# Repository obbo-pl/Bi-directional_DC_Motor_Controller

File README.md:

# Bi-directional_DC_Motor_Controller
RC Bi-directional DC Motor Speed Controller

##### Main features:

- supply voltage: 7.0 - 20.0V,
- average current: 10A, maximum instantaneous current: 140A,
- BEC 5V 1,2A,
- protection against reverse battery polarity,
- on/off switch controlled by logic level,
- calibration of the adjustment range with automatic saving of settings,
- protection against engine starting when starting the system,
- Cut-off, engine shutdown or speed reduction,
- choice of: linear and nonlinear RPM control characteristics,
- speed regulation smoothing filter,
- Fail-safe, engine shutdown in the event of signal loss,
- 3 quick configuration jumpers,
- brake,
- parameter configuration via serial port (9600bps).

### Hardware & Firmware.

These sections provide information on building a hardware, including schematics, PCBs, and firmware.

For more information: [www.obbo.pl](http://obbo.pl/dc-controller)

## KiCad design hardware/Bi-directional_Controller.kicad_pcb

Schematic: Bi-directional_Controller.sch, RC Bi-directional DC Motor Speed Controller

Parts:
B1: bead; L_0805K
C1, C9: 100n; C_0805_2012Metric
C4, C5, C8, C10: 100n; C_Disc_D5.0mm_W2.5mm_P5.00mm_PAD
C6, C7: 15p; C_0805_2012Metric
C11: 100u/35V; CP_Elec_6.3x5.9
C12: 1000u/10V; CP_Elec_10x10
D1: B340; D_SMB
D2: LED; LED_0805_2012Metric_Pad1.15x1.40mm_HandSolder
D3: 4V7; D_MiniMELF
D4: 8v2; D_MiniMELF
J1: ON/OFF; PinHeader_1x02_P2.54mm_Vertical_PAD
J2: Conn_01x06; PinHeader_1x06_P2.54mm_Vertical_PAD
J3: Conn_02x03_Odd_Even; PinHeader_2x03_P2.54mm_Vertical_SMD
J7: BAT 12V; TerminalBlock_Degson_DG128-5.0-02P
J8: CH1; PinHeader_1x03_P2.54mm_Vertical_PAD
J13: MOTOR; TerminalBlock_Degson_DG128-5.0-02P
J14: Serial; PinHeader_1x03_P2.54mm_Vertical_PAD
L1: 100uH; L_SMD_Ferrite_X13mm_Y10mm_H5mm_HandSoldering
Q1, Q2: BSS138; SOT-23
Q3, Q4, Q5, Q6: AOD403; TO-252-2-DPAK
Q7, Q8, Q9, Q10: AOD240; TO-252-2-DPAK
Q12: AO6401A; TSOP-6_1.65x3.05mm_P0.95mm
R1, R18: 330; R_0805_2012Metric
R2, R3, R11, R15: 10k; R_0805_2012Metric
R10: 22k*; R_0805_2012Metric
R12, R26: 4k7; R_0805_2012Metric
R13, R14, R24, R25: 22k; R_0805_2012Metric
R16: 11k*; R_0805_2012Metric
R17, R20: 220; R_0805_2012Metric
R19, R21: 22k; R_Axial_DIN0207_L6.3mm_D2.5mm_P10.16mm_Horizontal_PAD
R22, R23: 220; R_Axial_DIN0207_L6.3mm_D2.5mm_P10.16mm_Horizontal_PAD
SW1: RESET; SW_SPST_PTS645
U1: LM2576HVS-5; TO-263-5_TabPin6
U2: ATmega8-16AU; TQFP-32_7x7mm_P0.8mm
Y1: 16MHz; Crystal_SMD_HC49-SD_HandSoldering

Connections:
+5V: B1.1, C5.1, C12.1, J2.4, J8.2, L1.2, R11.1, R15.2, U2.4 (VCC), U2.6 (VCC)
+12V: C10.1, C11.1, D4.1 (K), Q12.4, R2.2, R10.1, U1.1 (VIN)
CH1: R1.1, U2.9 (PD5)
DIR_L: R20.2, U2.13 (PB1)
DIR_R: R17.2, U2.14 (PB2)
GND: C1.2, C4.2, C5.2, C6.2, C7.2, C8.2, C9.2, C10.2, C11.2, C12.2, D1.2 (A), D2.1 (K), D3.2 (A), J1.1, J2.5, J3.2, J3.4, J3.6, J7.2, J8.1, J14.3, Q1.2 (S), Q2.2 (S), Q7.3, Q8.3, Q9.3, Q10.3, R3.1, R12.2, R16.2, R19.1, R21.2, R24.1, R25.1, R26.1, SW1.1, U1.3 (GND), U2.3 (GND), U2.5 (GND), U2.21 (AGND)
unnamed: B1.2, C8.1, U2.18 (AVCC)
unnamed: C4.1, J2.6, R11.2, SW1.2, U2.29 (PC6/~RESET)
unnamed: C6.1, U2.7 (PB6/XTAL1), Y1.1
unnamed: C7.1, U2.8 (PB7/XTAL2), Y1.2
unnamed: C9.1, U2.20 (AREF)
unnamed: D1.1 (K), L1.1, U1.2 (OUT)
unnamed: D2.2 (A), R18.2
unnamed: D4.2 (A), Q12.3, R3.2
unnamed: J1.2, R2.1, U1.5 (~ON~/OFF)
unnamed: J2.1, U2.15 (PB3)
unnamed: J2.2, U2.16 (PB4)
unnamed: J2.3, U2.17 (PB5)
unnamed: J3.1, U2.12 (PB0)
unnamed: J3.3, U2.11 (PD7)
unnamed: J3.5, U2.10 (PD6)
unnamed: J8.3, R1.2
unnamed: J13.1, Q3.2, Q4.2, Q7.2, Q8.2
unnamed: J13.2, Q5.2, Q6.2, Q9.2, Q10.2
unnamed: J14.1, U2.30 (PD0)
unnamed: J14.2, U2.31 (PD1)
unnamed: Q1.1 (G), R17.1, R19.2
unnamed: Q1.3 (D), Q3.1, Q4.1, R13.1
unnamed: Q2.1 (G), R20.1, R21.1
unnamed: Q2.3 (D), Q5.1, Q6.1, R14.1
unnamed: Q7.1, Q8.1, R22.2, R24.2
unnamed: Q9.1, Q10.1, R23.2, R25.2
unnamed: R15.1, R16.1, R26.2, U1.4 (FB)
unnamed: R18.1, U2.1 (PD3)
PULS_L: R22.1, U2.25 (PC2)
PULS_R: R23.1, U2.24 (PC1)
V_BAT: J7.1, Q3.3, Q4.3, Q5.3, Q6.3, Q12.1, Q12.2, Q12.5, Q12.6, R13.2, R14.2
V_TEST: C1.1, D3.1 (K), R10.2, R12.1, U2.26 (PC3)

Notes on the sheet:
ATmega328
68k* (Atmega328)

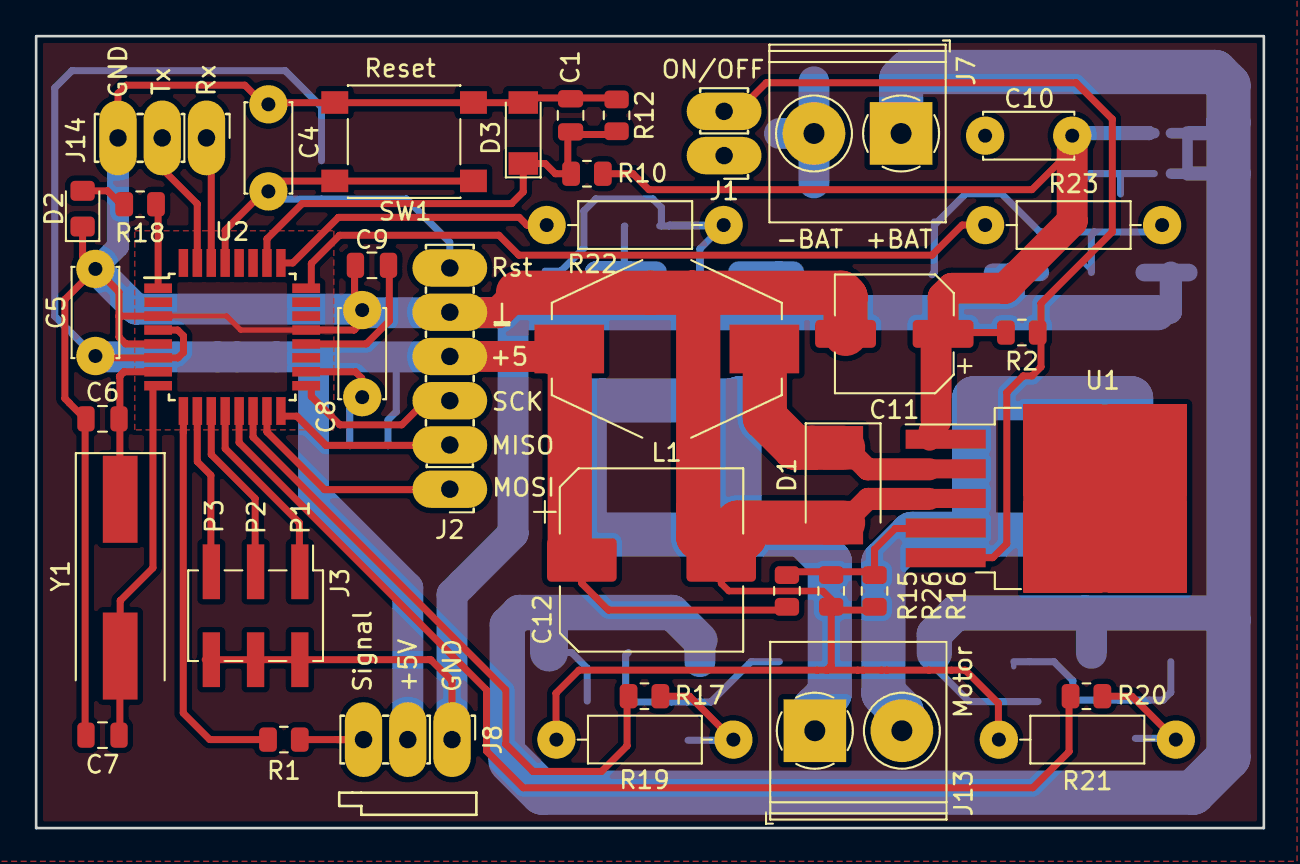
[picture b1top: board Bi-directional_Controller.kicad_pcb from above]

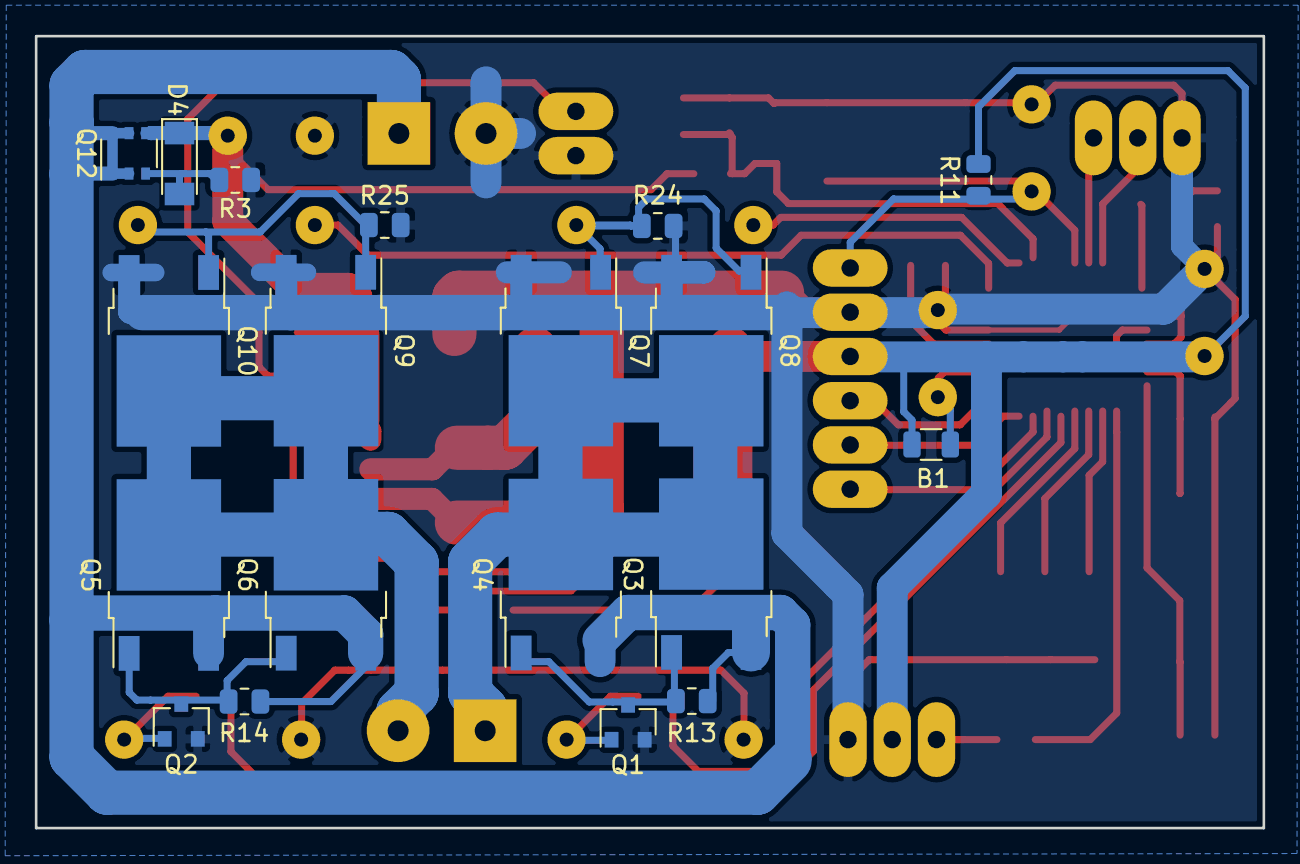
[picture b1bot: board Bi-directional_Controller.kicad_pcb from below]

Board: 2 copper layers, 70.5 x 45.5 mm, 58 parts (19 on the bottom side), 38 nets.

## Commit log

2019-11-24 symbols update
2019-12-29 new terminal commands
2019-12-30 added function to store calibration
2020-01-02 disable motor in service mode
2020-01-02 new terminal command @MDS
2020-07-14 uart_terminal split into separate libraries, support for Atmega328
2020-07-14 support for Atmega328
2020-07-15 simplified configuration file
2020-07-15 improved ADC conversion
2020-07-19 motor brake option added
2020-07-21 bridge control in a separate file
2020-07-30 added error state signaling
2020-08-02 pulse length unit changed to microseconds
2020-08-02 calculate PWM only after changing the value
2020-08-24 bridge control based on timer interrupts
2020-08-24 closer loop when seeking a signal
2023-03-04 symbol update
